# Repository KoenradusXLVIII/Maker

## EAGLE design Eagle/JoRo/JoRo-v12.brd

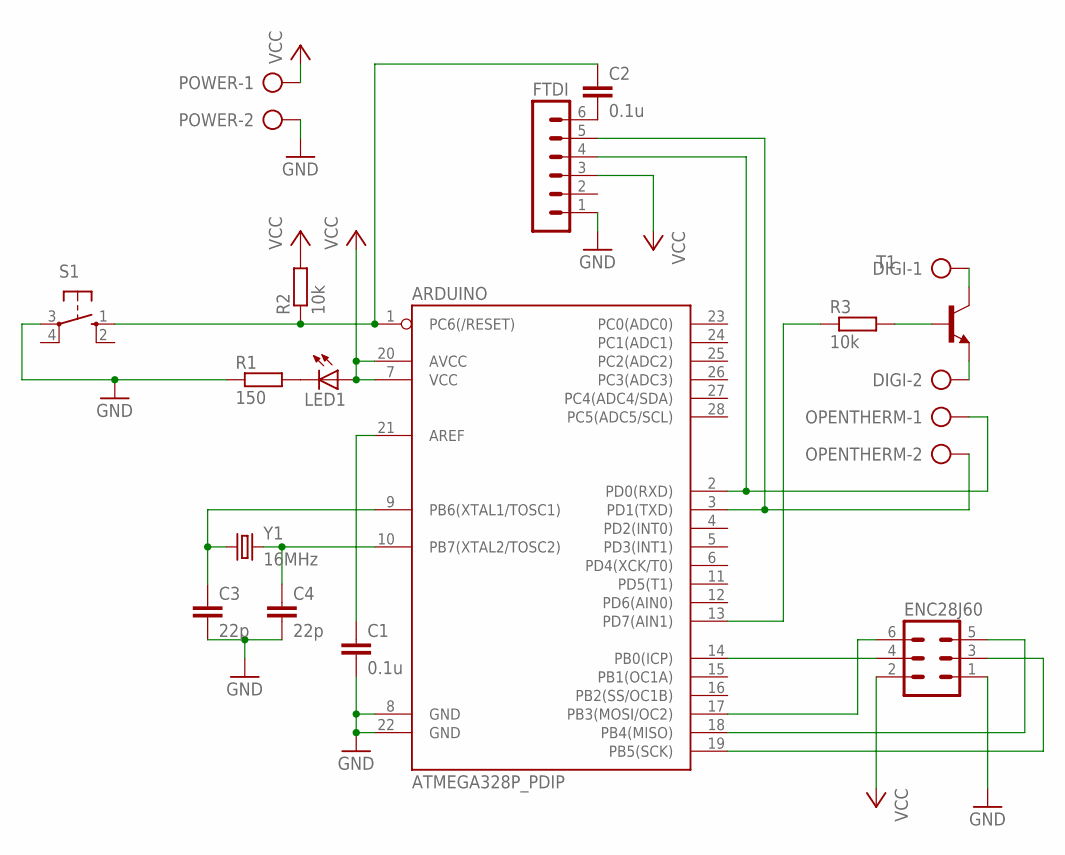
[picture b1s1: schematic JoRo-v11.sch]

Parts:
ARDUINO: ATMEGA328P_PDIP; DIL28-3
C1, C2: 0.1u; C025-024X044
C3, C4: 22p; C025-024X044
DIGI: AK500/2
ENC28J60: MA03-2
FTDI: MA06-1
LED1: LED3MM
OPENTHERM: AK500/2
POWER: AK500/2
R1: 150; 0207/7
R2, R3: 10k; 0207/7
S1: 10-XX; B3F-10XX
T1: BC548-NPN-TO92-CBE; TO92-CBE
Y1: 16MHz; HC49US

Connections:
GND: ARDUINO.8 (GND), ARDUINO.22 (GND), C1.2, C3.2, C4.2, ENC28J60.1, FTDI.1, POWER.2, R1.1, S1.3
unnamed: ARDUINO.1 (PC6(/RESET)), C2.1, R2.1, S1.1 (S)
unnamed: ARDUINO.9 (PB6(XTAL1/TOSC1)), C3.1, Y1.1
unnamed: ARDUINO.10 (PB7(XTAL2/TOSC2)), C4.1, Y1.2
unnamed: ARDUINO.21 (AREF), C1.1
unnamed: LED1.K (C), R1.2
unnamed: ARDUINO.19 (PB5(SCK)), ENC28J60.3
unnamed: C2.2, FTDI.6
unnamed: ARDUINO.3 (PD1(TXD)), FTDI.5, OPENTHERM.2
unnamed: ARDUINO.2 (PD0(RXD)), FTDI.4, OPENTHERM.1
unnamed: ARDUINO.14 (PB0(ICP)), ENC28J60.4
unnamed: ARDUINO.17 (PB3(MOSI/OC2)), ENC28J60.6
unnamed: ARDUINO.18 (PB4(MISO)), ENC28J60.5
unnamed: R3.2, T1.B
unnamed: ARDUINO.13 (PD7(AIN1)), R3.1
unnamed: DIGI.1, T1.C
unnamed: DIGI.2, T1.E
VCC: ARDUINO.7 (VCC), ARDUINO.20 (AVCC), ENC28J60.2, FTDI.3, LED1.A, POWER.1, R2.2

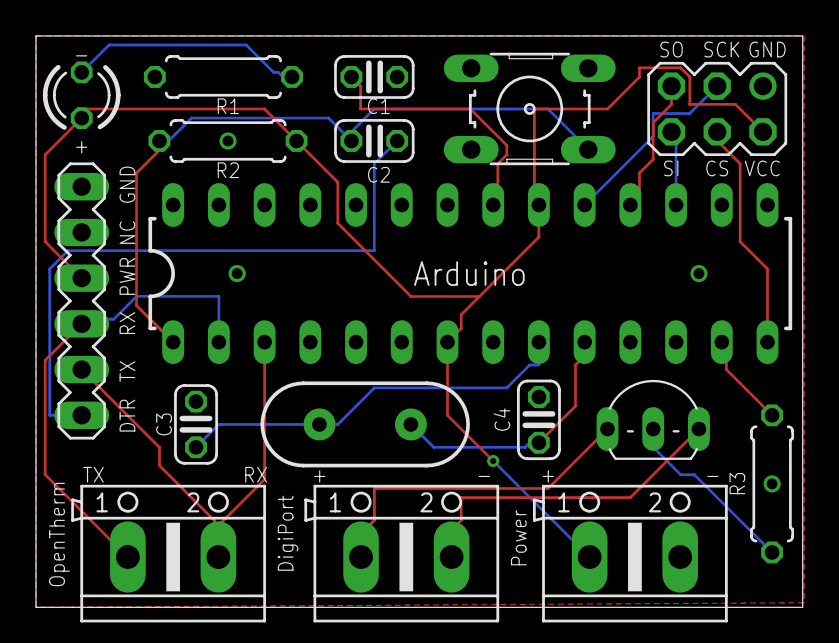
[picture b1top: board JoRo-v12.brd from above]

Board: 2 copper layers, 42.6 x 31.7 mm, 17 parts (0 on the bottom side), 18 nets.

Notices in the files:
parts and their libraries:
SparkFun-DigitalIC: Licensing: CC v3.0 Share-Alike You are welcome to use this library for commercial purposes.
